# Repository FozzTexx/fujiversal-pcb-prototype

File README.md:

## Prototype board for doing bus/card/cartridge bringups

Uses two development boards:

* [Waveshare Core2350B](https://www.waveshare.com/core2350b.htm)
* [Freenove ESP32-S3 CAM](https://store.freenove.com/products/fnk0085) dual USB with microSD on the back

The ESP32-S3 board may require soldering to get the microSD card working.

<insert details about soldering microSD pin to ground here>

These boards or clones of them are readily available from a variety of retailers.

### Core2350B

* https://www.amazon.com/dp/B0FHHC6RJZ

### ESP32-S3 dual USB with microSD

* https://www.amazon.com/dp/B0F4DKTBR9
* https://www.aliexpress.us/item/3256807465857681.html
* https://www.aliexpress.us/item/3256810232350882.html

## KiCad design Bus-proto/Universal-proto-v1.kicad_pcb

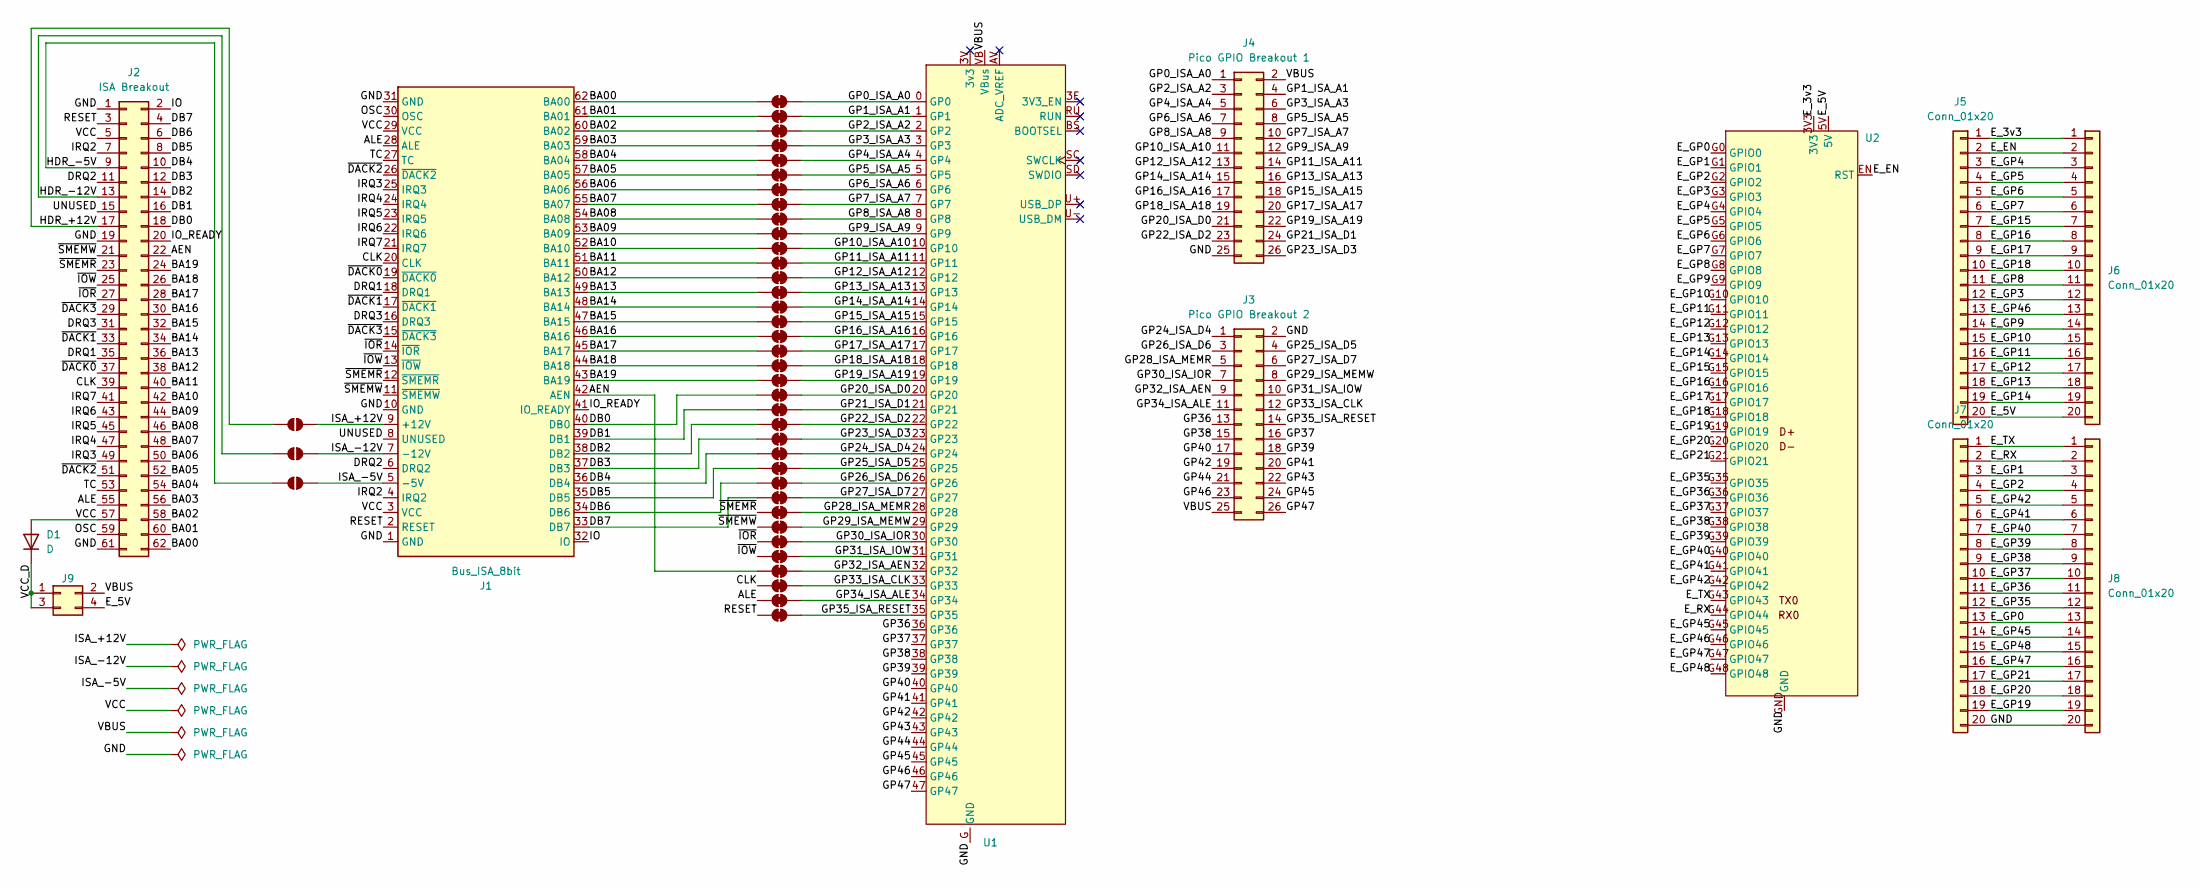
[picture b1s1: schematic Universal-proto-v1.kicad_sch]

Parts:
D1: D; D_DO-15_P15.24mm_Horizontal
J1: Bus_ISA_8bit; ISA_8bit
J2: ISA Breakout; PinHeader_2x31_P2.54mm_Vertical
J3: Pico GPIO Breakout 2; PinHeader_2x13_P2.54mm_Vertical
J4: Pico GPIO Breakout 1; PinHeader_2x13_P2.54mm_Vertical
J5, J6, J7, J8: Conn_01x20; PinHeader_1x20_P2.54mm_Vertical
J9: Conn_02x02_Odd_Even; PinHeader_2x02_P2.54mm_Vertical
JP1, JP2, JP3, JP4, JP5, JP6, JP7, JP8, JP9, JP10, JP11, JP12, JP13, JP14, JP15, JP16, JP17, JP18, JP19, JP20, JP21, JP22, JP23, JP24, JP25, JP26, JP27, JP28, JP29, JP30, JP31, JP32, JP33, JP34, JP35, JP36: SolderJumper_2_Bridged; SolderJumper-2_P1.3mm_Bridged_RoundedPad1.0x1.5mm
JP37, JP38, JP39: SolderJumper_2_Open; SolderJumper-2_P1.3mm_Open_Pad1.0x1.5mm
U1: WaveShare-Core-RP2350B
U2: ESP32-S3-CAM

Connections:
/AEN: J1.42 (AEN), J2.22, JP33.1 (A)
/ALE: J1.28 (ALE), J2.55, JP35.1 (A)
/BA00: J1.62 (BA00), J2.62, JP1.1 (A)
/BA01: J1.61 (BA01), J2.60, JP2.1 (A)
/BA02: J1.60 (BA02), J2.58, JP3.1 (A)
/BA03: J1.59 (BA03), J2.56, JP4.1 (A)
/BA04: J1.58 (BA04), J2.54, JP5.1 (A)
/BA05: J1.57 (BA05), J2.52, JP6.1 (A)
/BA06: J1.56 (BA06), J2.50, JP7.1 (A)
/BA07: J1.55 (BA07), J2.48, JP8.1 (A)
/BA08: J1.54 (BA08), J2.46, JP9.1 (A)
/BA09: J1.53 (BA09), J2.44, JP10.1 (A)
/BA10: J1.52 (BA10), J2.42, JP11.1 (A)
/BA11: J1.51 (BA11), J2.40, JP12.1 (A)
/BA12: J1.50 (BA12), J2.38, JP13.1 (A)
/BA13: J1.49 (BA13), J2.36, JP14.1 (A)
/BA14: J1.48 (BA14), J2.34, JP15.1 (A)
/BA15: J1.47 (BA15), J2.32, JP16.1 (A)
/BA16: J1.46 (BA16), J2.30, JP17.1 (A)
/BA17: J1.45 (BA17), J2.28, JP18.1 (A)
/BA18: J1.44 (BA18), J2.26, JP19.1 (A)
/BA19: J1.43 (BA19), J2.24, JP20.1 (A)
/CLK: J1.20 (CLK), J2.39, JP34.1 (A)
/DB0: J1.40 (DB0), J2.18, JP21.1 (A)
/DB1: J1.39 (DB1), J2.16, JP22.1 (A)
/DB2: J1.38 (DB2), J2.14, JP23.1 (A)
/DB3: J1.37 (DB3), J2.12, JP24.1 (A)
/DB4: J1.36 (DB4), J2.10, JP25.1 (A)
/DB5: J1.35 (DB5), J2.8, JP26.1 (A)
/DB6: J1.34 (DB6), J2.6, JP27.1 (A)
/DB7: J1.33 (DB7), J2.4, JP28.1 (A)
/DRQ1: J1.18 (DRQ1), J2.35
/DRQ2: J1.6 (DRQ2), J2.11
/DRQ3: J1.16 (DRQ3), J2.31
/E_3v3: J5.1, J6.1, U2.3V3
/E_5V: J5.20, J6.20, J9.4, U2.5V
/E_EN: J5.2, J6.2, U2.EN (RST)
/E_GP0: J7.13, J8.13, U2.G0 (GPIO0)
/E_GP1: J7.3, J8.3, U2.G1 (GPIO1)
/E_GP2: J7.4, J8.4, U2.G2 (GPIO2)
/E_GP3: J5.12, J6.12, U2.G3 (GPIO3)
/E_GP4: J5.3, J6.3, U2.G4 (GPIO4)
/E_GP5: J5.4, J6.4, U2.G5 (GPIO5)
/E_GP6: J5.5, J6.5, U2.G6 (GPIO6)
/E_GP7: J5.6, J6.6, U2.G7 (GPIO7)
/E_GP8: J5.11, J6.11, U2.G8 (GPIO8)
/E_GP9: J5.14, J6.14, U2.G9 (GPIO9)
/E_GP10: J5.15, J6.15, U2.G10 (GPIO10)
/E_GP11: J5.16, J6.16, U2.G11 (GPIO11)
/E_GP12: J5.17, J6.17, U2.G12 (GPIO12)
/E_GP13: J5.18, J6.18, U2.G13 (GPIO13)
/E_GP14: J5.19, J6.19, U2.G14 (GPIO14)
/E_GP15: J5.7, J6.7, U2.G15 (GPIO15)
/E_GP16: J5.8, J6.8, U2.G16 (GPIO16)
/E_GP17: J5.9, J6.9, U2.G17 (GPIO17)
/E_GP18: J5.10, J6.10, U2.G18 (GPIO18)
/E_GP19: J7.19, J8.19, U2.G19 (GPIO19)
/E_GP20: J7.18, J8.18, U2.G20 (GPIO20)
/E_GP21: J7.17, J8.17, U2.G21 (GPIO21)
/E_GP35: J7.12, J8.12, U2.G35 (GPIO35)
/E_GP36: J7.11, J8.11, U2.G36 (GPIO36)
/E_GP37: J7.10, J8.10, U2.G37 (GPIO37)
/E_GP38: J7.9, J8.9, U2.G38 (GPIO38)
/E_GP39: J7.8, J8.8, U2.G39 (GPIO39)
/E_GP40: J7.7, J8.7, U2.G40 (GPIO40)
/E_GP41: J7.6, J8.6, U2.G41 (GPIO41)
/E_GP42: J7.5, J8.5, U2.G42 (GPIO42)
/E_GP45: J7.14, J8.14, U2.G45 (GPIO45)
/E_GP46: J5.13, J6.13, U2.G46 (GPIO46)
/E_GP47: J7.16, J8.16, U2.G47 (GPIO47)
/E_GP48: J7.15, J8.15, U2.G48 (GPIO48)
/E_RX: J7.2, J8.2, U2.G44 (GPIO44)
/E_TX: J7.1, J8.1, U2.G43 (GPIO43)
/GND: J1.1 (GND), J1.10 (GND), J1.31 (GND), J2.1, J2.19, J2.61, J3.2, J4.25, J7.20, J8.20, U1.G (GND), U2.GND
/GP0_ISA_A0: J4.1, JP1.2 (B), U1.0 (GP0)
/GP1_ISA_A1: J4.4, JP2.2 (B), U1.1 (GP1)
/GP2_ISA_A2: J4.3, JP3.2 (B), U1.2 (GP2)
/GP3_ISA_A3: J4.6, JP4.2 (B), U1.3 (GP3)
/GP4_ISA_A4: J4.5, JP5.2 (B), U1.4 (GP4)
/GP5_ISA_A5: J4.8, JP6.2 (B), U1.5 (GP5)
/GP6_ISA_A6: J4.7, JP7.2 (B), U1.6 (GP6)
/GP7_ISA_A7: J4.10, JP8.2 (B), U1.7 (GP7)
/GP8_ISA_A8: J4.9, JP9.2 (B), U1.8 (GP8)
/GP9_ISA_A9: J4.12, JP10.2 (B), U1.9 (GP9)
/GP10_ISA_A10: J4.11, JP11.2 (B), U1.10 (GP10)
/GP11_ISA_A11: J4.14, JP12.2 (B), U1.11 (GP11)
/GP12_ISA_A12: J4.13, JP13.2 (B), U1.12 (GP12)
/GP13_ISA_A13: J4.16, JP14.2 (B), U1.13 (GP13)
/GP14_ISA_A14: J4.15, JP15.2 (B), U1.14 (GP14)
/GP15_ISA_A15: J4.18, JP16.2 (B), U1.15 (GP15)
/GP16_ISA_A16: J4.17, JP17.2 (B), U1.16 (GP16)
/GP17_ISA_A17: J4.20, JP18.2 (B), U1.17 (GP17)
/GP18_ISA_A18: J4.19, JP19.2 (B), U1.18 (GP18)
/GP19_ISA_A19: J4.22, JP20.2 (B), U1.19 (GP19)
/GP20_ISA_D0: J4.21, JP21.2 (B), U1.20 (GP20)
/GP21_ISA_D1: J4.24, JP22.2 (B), U1.21 (GP21)
/GP22_ISA_D2: J4.23, JP23.2 (B), U1.22 (GP22)
/GP23_ISA_D3: J4.26, JP24.2 (B), U1.23 (GP23)
/GP24_ISA_D4: J3.1, JP25.2 (B), U1.24 (GP24)
/GP25_ISA_D5: J3.4, JP26.2 (B), U1.25 (GP25)
/GP26_ISA_D6: J3.3, JP27.2 (B), U1.26 (GP26)
/GP27_ISA_D7: J3.6, JP28.2 (B), U1.27 (GP27)
/GP28_ISA_MEMR: J3.5, JP29.2 (B), U1.28 (GP28)
/GP29_ISA_MEMW: J3.8, JP30.2 (B), U1.29 (GP29)
/GP30_ISA_IOR: J3.7, JP31.2 (B), U1.30 (GP30)
/GP31_ISA_IOW: J3.10, JP32.2 (B), U1.31 (GP31)
/GP32_ISA_AEN: J3.9, JP33.2 (B), U1.32 (GP32)
/GP33_ISA_CLK: J3.12, JP34.2 (B), U1.33 (GP33)
/GP34_ISA_ALE: J3.11, JP35.2 (B), U1.34 (GP34)
/GP35_ISA_RESET: J3.14, JP36.2 (B), U1.35 (GP35)
/GP36: J3.13, U1.36 (GP36)
/GP37: J3.16, U1.37 (GP37)
/GP38: J3.15, U1.38 (GP38)
/GP39: J3.18, U1.39 (GP39)
/GP40: J3.17, U1.40 (GP40)
/GP41: J3.20, U1.41 (GP41)
/GP42: J3.19, U1.42 (GP42)
/GP43: J3.22, U1.43 (GP43)
/GP44: J3.21, U1.44 (GP44)
/GP45: J3.24, U1.45 (GP45)
/GP46: J3.23, U1.46 (GP46)
/GP47: J3.26, U1.47 (GP47)
/HDR_+12V: J2.17, JP37.1 (A)
/HDR_-5V: J2.9, JP39.1 (A)
/HDR_-12V: J2.13, JP38.1 (A)
/IO: J1.32 (IO), J2.2
/IO_READY: J1.41 (IO_READY), J2.20
/IRQ2: J1.4 (IRQ2), J2.7
/IRQ3: J1.25 (IRQ3), J2.49
/IRQ4: J1.24 (IRQ4), J2.47
/IRQ5: J1.23 (IRQ5), J2.45
/IRQ6: J1.22 (IRQ6), J2.43
/IRQ7: J1.21 (IRQ7), J2.41
/ISA_+12V: J1.9 (+12V), JP37.2 (B)
/ISA_-5V: J1.5 (-5V), JP39.2 (B)
/ISA_-12V: J1.7 (-12V), JP38.2 (B)
/OSC: J1.30 (OSC), J2.59
/RESET: J1.2 (RESET), J2.3, JP36.1 (A)
/TC: J1.27 (TC), J2.53
/UNUSED: J1.8 (UNUSED), J2.15
/VBUS: J3.25, J4.2, J9.2, U1.VB (VBus)
/VCC: D1.2 (A), J1.3 (VCC), J1.29 (VCC), J2.5, J2.57
/VCC_D: D1.1 (K), J9.1, J9.3
/~DACK0: J1.19 (~DACK0), J2.37
/~DACK1: J1.17 (~DACK1), J2.33
/~DACK2: J1.26 (~DACK2), J2.51
/~DACK3: J1.15 (~DACK3), J2.29
/~IOR: J1.14 (~IOR), J2.27, JP31.1 (A)
/~IOW: J1.13 (~IOW), J2.25, JP32.1 (A)
/~SMEMR: J1.12 (~SMEMR), J2.23, JP29.1 (A)
/~SMEMW: J1.11 (~SMEMW), J2.21, JP30.1 (A)

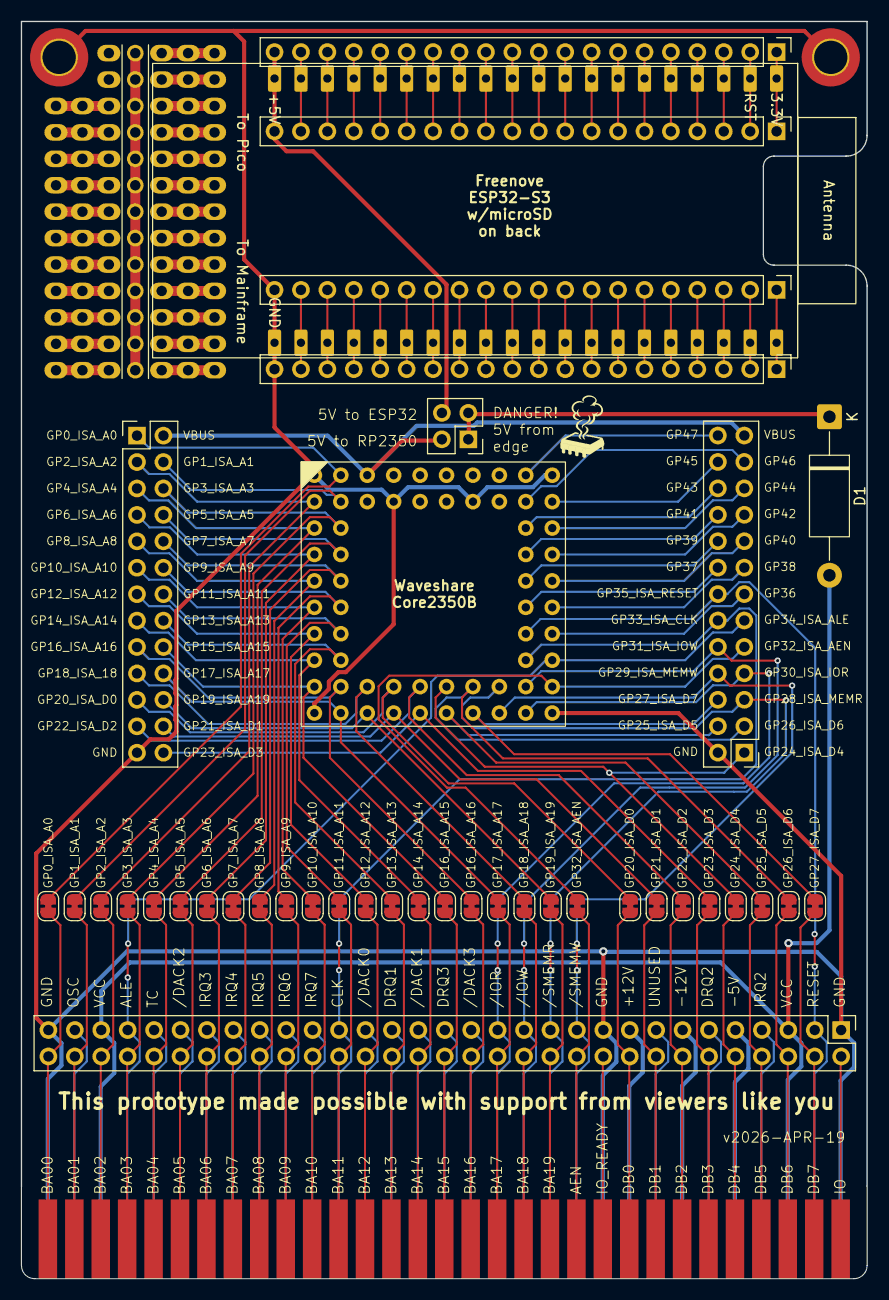
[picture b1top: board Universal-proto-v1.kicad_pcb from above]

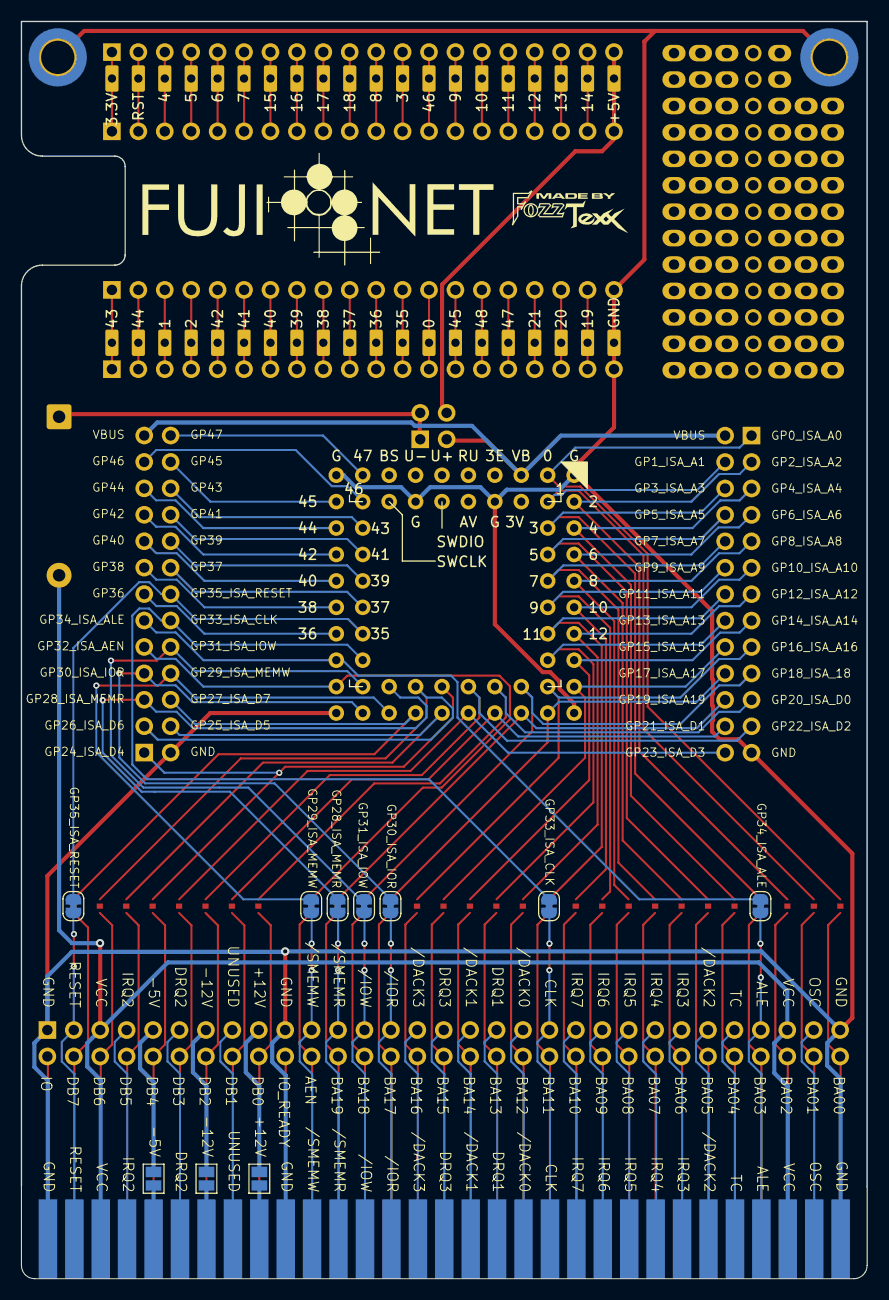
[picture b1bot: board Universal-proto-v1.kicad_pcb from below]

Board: 2 copper layers, 81.3 x 120.8 mm, 51 parts (10 on the bottom side), 151 nets.

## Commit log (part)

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2026-03-23 Layout with ISA bus, Core2350, and debug/mod headers
2026-03-23 Add fujinet-parts submodule
2026-03-24 Start work on PCB
2026-03-24 Connect ISA pins to solder jumpers
2026-03-24 zig-zag around GPIO breakout, ISA connected to Core2350
2026-03-25 GPIO breakout is routed
2026-03-25 Connect some grounds
2026-03-25 Most everything connected.
2026-03-25 Everything connected.
2026-03-25 Added GPIO labels
2026-03-25 Lots of labels
2026-03-25 Fix order of front labels
2026-03-26 Pre-split of GPIO breakout
2026-03-26 Everything seems to fit
2026-03-27 Fixups
2026-03-27 Core2350 connected to ISA bus
2026-03-27 Everything connected
2026-03-27 Fixed up text warnings
2026-03-27 Created 8bit ISA footprint in parts.pretty
2026-03-27 Added logos
2026-03-28 Added warning, diode, jumpers for 5V from edge
2026-03-29 Cleanups
2026-03-29 Move bus prototype one level deeper
2026-03-29 Move shared files back to root
2026-03-29 Working on CoCo adapter
2026-03-29 Clean up edge connectors
2026-03-29 Routed CoCo adapter
2026-03-30 Add CoCo adapter mounting holes
2026-04-01 Add MSX adapter
2026-04-01 Move logo
2026-04-01 Remove traces from protoboard back
2026-04-02 Added README.md
2026-04-02 M3 mounting holes with ground connection
2026-04-02 Update version date
2026-04-02 M3 mounting holes with ground connection (#2)
2026-04-19 Fix edge cuts and labels
2026-04-20 Fix edges
2026-05-25 Add finger notch
